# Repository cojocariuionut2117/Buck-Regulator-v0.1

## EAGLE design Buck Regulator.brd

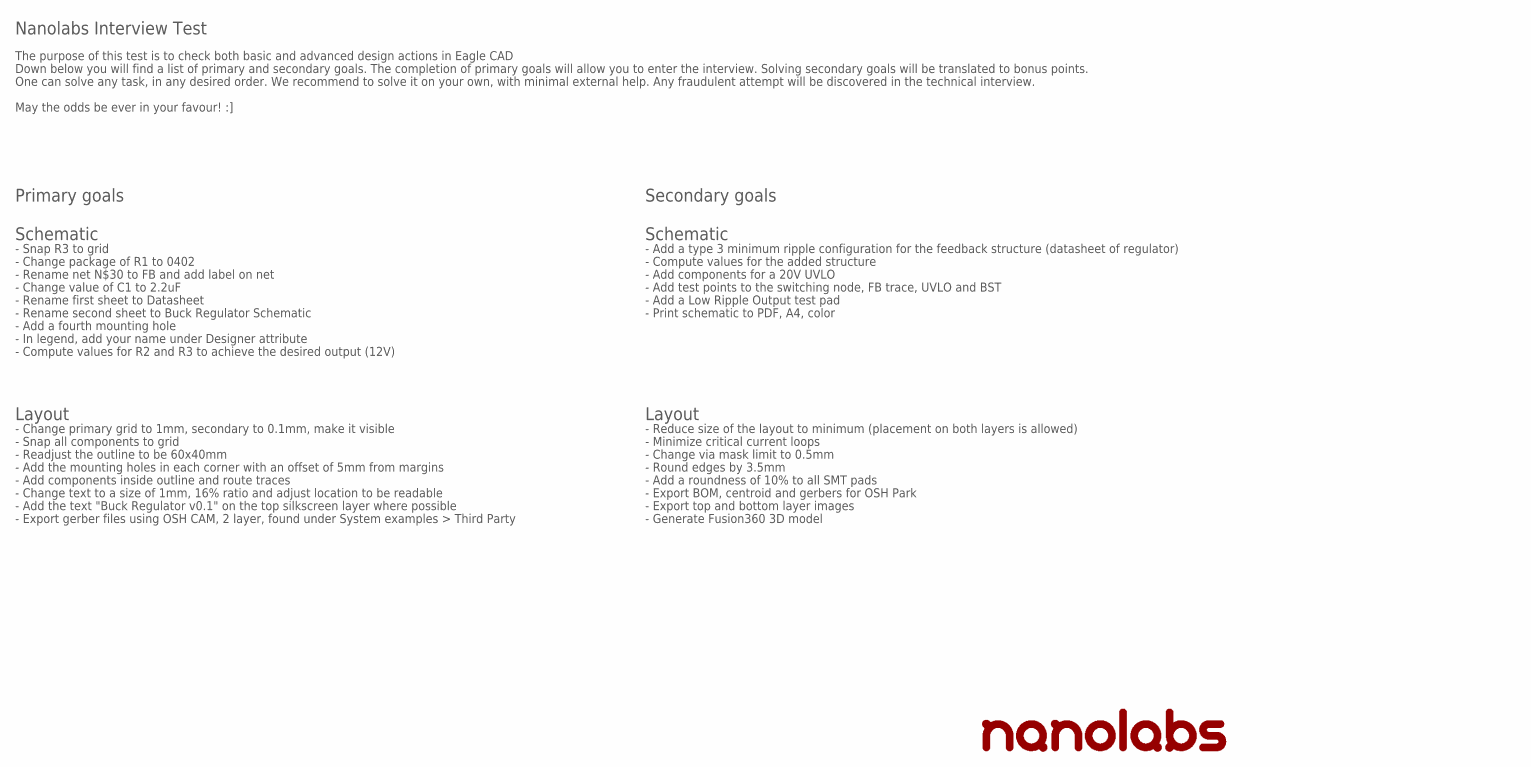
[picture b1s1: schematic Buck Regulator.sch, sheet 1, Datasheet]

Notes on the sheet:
Nanolabs Interview Test
The purpose of this test is to check both basic and advanced design actions in Eagle CAD
Down below you will find a list of primary and secondary goals. The completion of primary goals will allow you to enter the interview. Solving secondary goals will be translated to bonus points.
One can solve any task, in any desired order. We recommend to solve it on your own, with minimal external help. Any fraudulent attempt will be discovered in the technical interview.
May the odds be ever in your favour! :]
Primary goals
Secondary goals
- Snap R3 to grid
- Change package of R1 to 0402
- Rename net N$30 to FB and add label on net
- Rename first sheet to Datasheet
- Rename second sheet to Buck Regulator Schematic
- Add a fourth mounting hole
- In legend, add your name under Designer attribute
- Change value of C1 to 2.2uF
Schematic
- Change primary grid to 1mm, secondary to 0.1mm, make it visible
Layout
- Snap all components to grid
- Readjust the outline to be 60x40mm
- Add the mounting holes in each corner with an offset of 5mm from margins
- Add components inside outline and route traces
- Change text to a size of 1mm, 16% ratio and adjust location to be readable
- Add the text "Buck Regulator v0.1" on the top silkscreen layer where possible
- Export gerber files using OSH CAM, 2 layer, found under System examples > Third Party
- Add a type 3 minimum ripple configuration for the feedback structure (datasheet of regulator)
- Compute values for R2 and R3 to achieve the desired output (12V)
- Compute values for the added structure
- Add components for a 20V UVLO
- Add test points to the switching node, FB trace, UVLO and BST
- Add a Low Ripple Output test pad
- Reduce size of the layout to minimum (placement on both layers is allowed)
- Minimize critical current loops
- Change via mask limit to 0.5mm
- Round edges by 3.5mm
- Add a roundness of 10% to all SMT pads
- Export BOM, centroid and gerbers for OSH Park
- Print schematic to PDF, A4, color
- Export top and bottom layer images
- Generate Fusion360 3D model

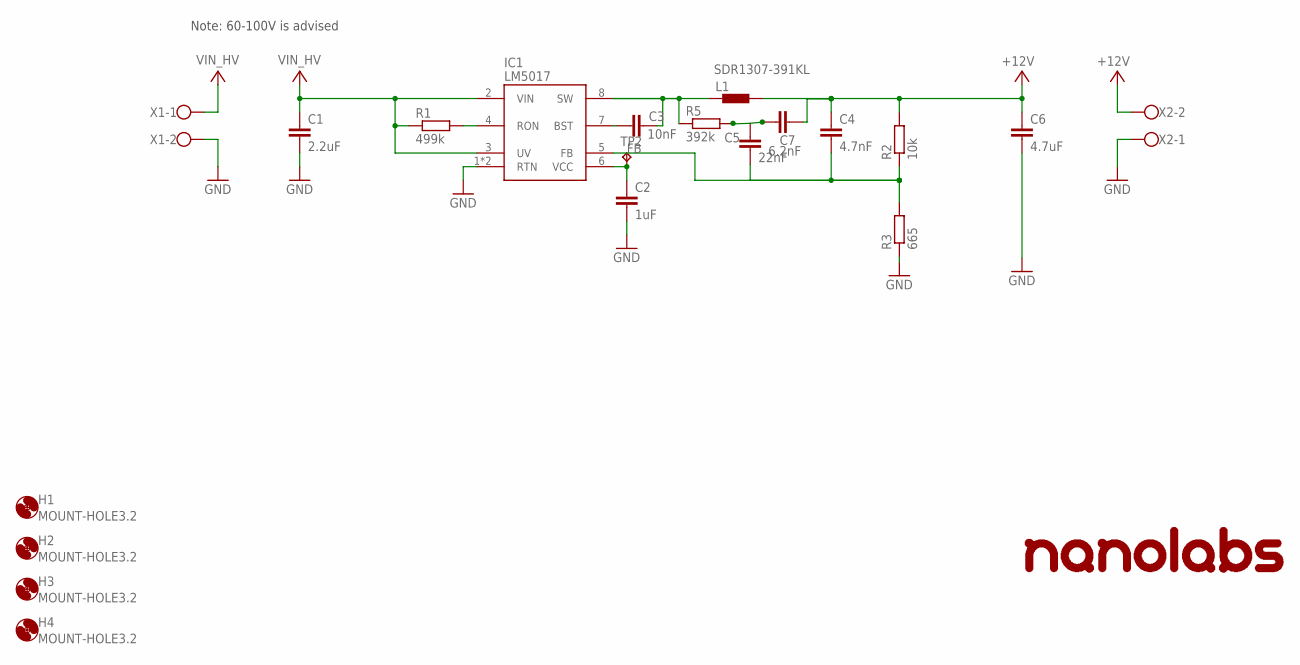
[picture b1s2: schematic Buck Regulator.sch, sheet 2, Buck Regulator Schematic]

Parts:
C1: 2.2uF; C1812
C2: 1uF; C0603
C3: 10nF; C0603
C4: 4.7nF; C0603
C5: 22nF; C2.5-2
C6: 4.7uF; C0603
C7: 6.2nF; C2.5-2
H1, H2, H3, H4: MOUNT-HOLE3.2; 3,2
IC1: LM5017; SO-08-EP
L1: SDR1307-391KL
R1: 499k; R0402
R2: 10k; R0603
R3: 665; R0603
R5: 392k; R0603
TP2: TPB1,27; B1,27
X1, X2: W237-102

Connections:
+12V: C4.1, C6.1, C7.2, L1.2, R2.2, X2.2
FB: C4.2, C5.2, IC1.5 (FB), R2.1, R3.2
GND: C1.2, C2.2, C6.2, IC1.1 (RTN), IC1.9 (RTN), R3.1, X1.2, X2.1
unnamed: C5.1, C7.1, R5.2
unnamed: C2.1, IC1.6 (VCC), TP2.TP
unnamed: C3.1, IC1.7 (BST)
unnamed: C3.2, IC1.8 (SW), L1.1, R5.1
unnamed: IC1.4 (RON), R1.2
VIN_HV: C1.1, IC1.2 (VIN), IC1.3 (UV), R1.1, X1.1

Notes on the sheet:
Note: 60-100V is advised

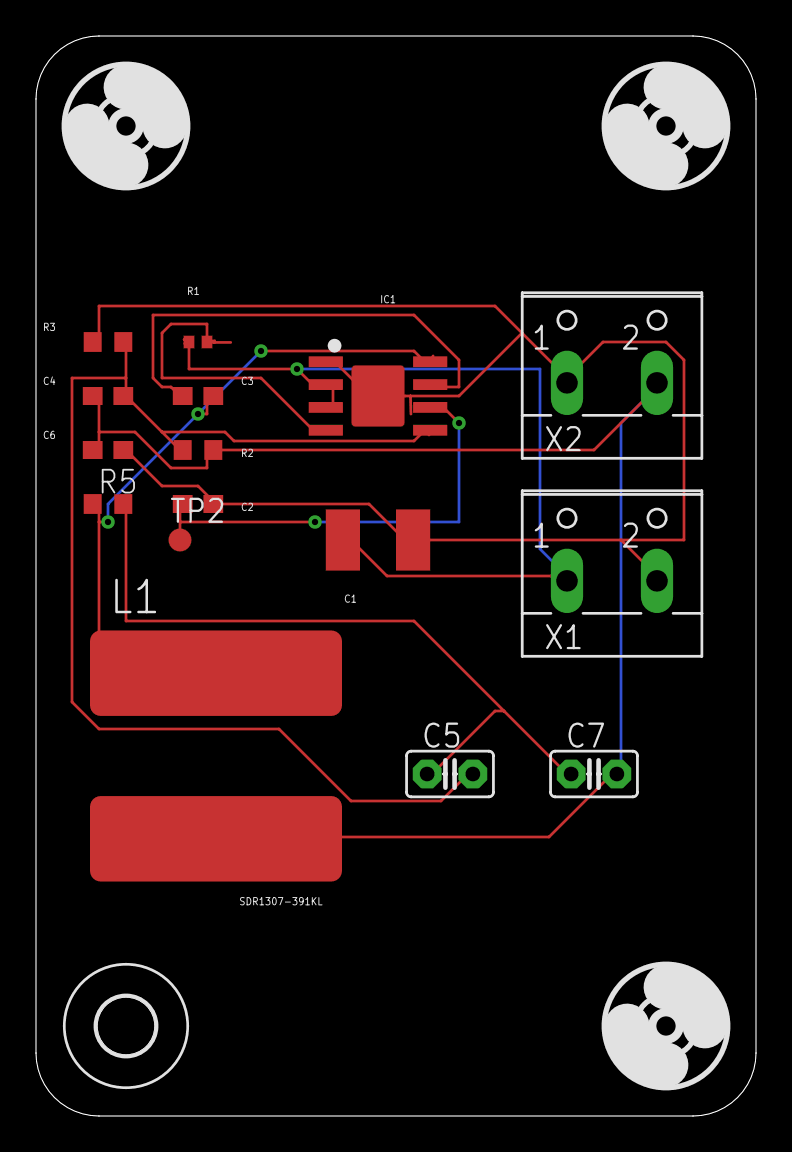
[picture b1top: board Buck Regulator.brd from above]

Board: 2 copper layers, 40.0 x 60.0 mm, 20 parts (0 on the bottom side), 9 nets.
